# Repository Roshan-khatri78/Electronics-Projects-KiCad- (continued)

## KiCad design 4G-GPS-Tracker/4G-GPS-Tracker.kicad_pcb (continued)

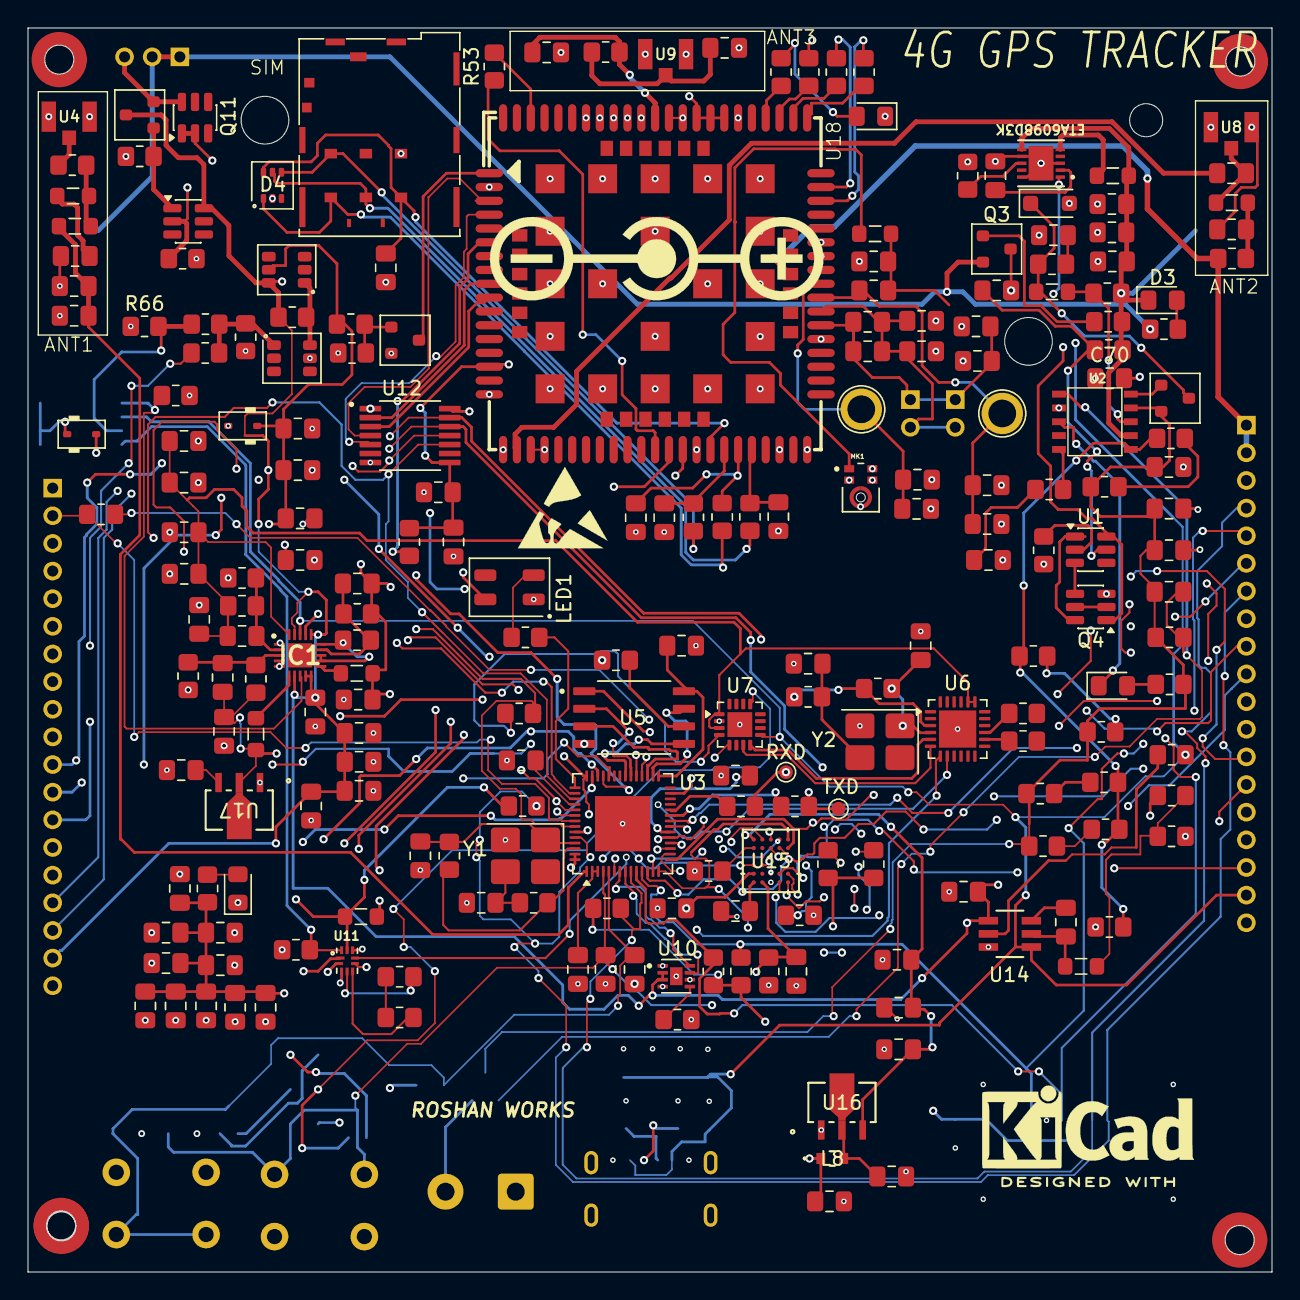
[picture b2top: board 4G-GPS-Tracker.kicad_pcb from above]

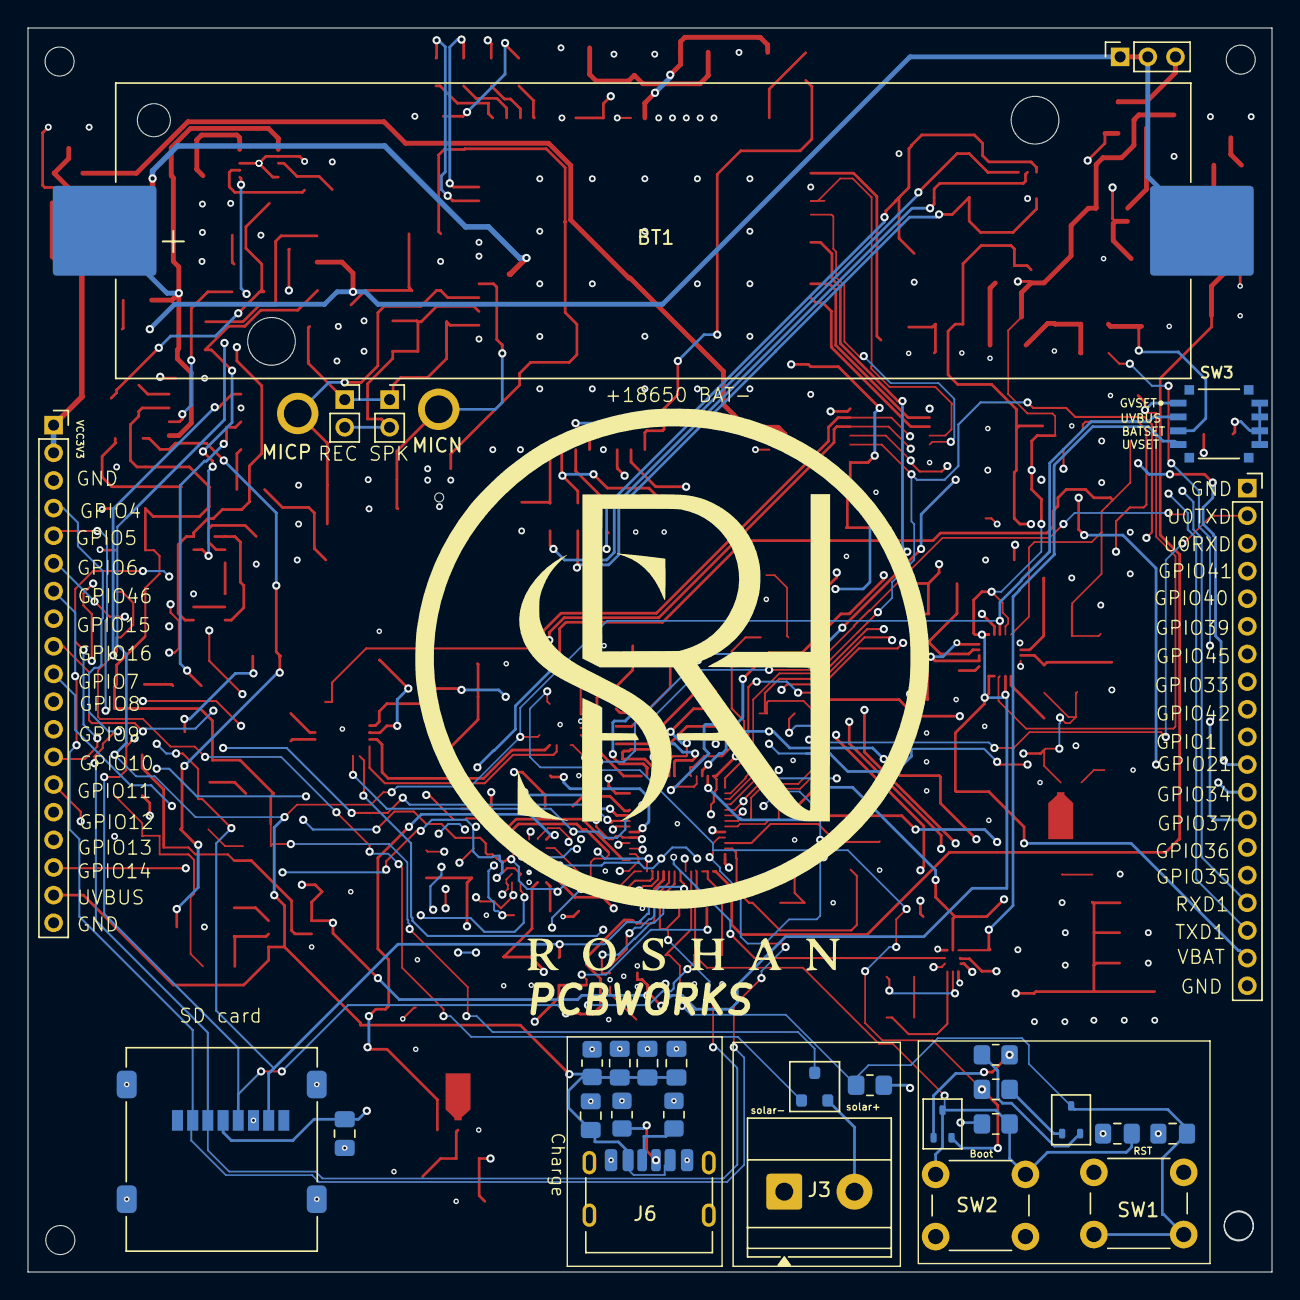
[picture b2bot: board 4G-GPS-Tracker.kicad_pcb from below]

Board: 4 copper layers, 90.0 x 90.0 mm, 248 parts (29 on the bottom side), 177 nets.

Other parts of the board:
ETA6098D3K: ETA6098D3K; DFN3x3-10_ETA-L
MICN: TestPoint; TestPoint_Plated_Hole_D2.0mm
MICP: TestPoint; TestPoint_Plated_Hole_D2.0mm
RXD: TestPoint; TestPoint_Pad_D1.0mm

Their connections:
/B+: ETA6098D3K.6 (BATS); also elsewhere on the board
/MIC N: MICN.1 (1_1); also elsewhere on the board
/MIC P: MICP.1 (1_1); also elsewhere on the board
/RXD1: RXD.1 (1_1); also elsewhere on the board
/UVBUS: ETA6098D3K.1 (IN); also elsewhere on the board
GND: ETA6098D3K.3 (PGND), ETA6098D3K.7 (AGND), ETA6098D3K.10 (AGND), ETA6098D3K.11 (AGND); also elsewhere on the board
unnamed 171: ETA6098D3K.8 (ISET); also elsewhere on the board
unnamed 172: ETA6098D3K.2 (PMID); also elsewhere on the board
unnamed 173: ETA6098D3K.5 (SW); also elsewhere on the board

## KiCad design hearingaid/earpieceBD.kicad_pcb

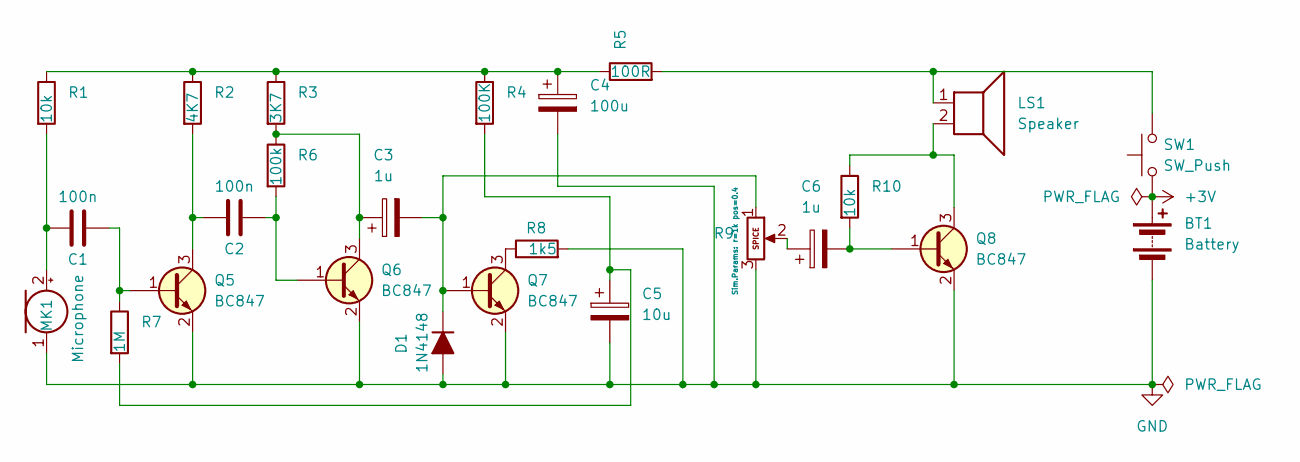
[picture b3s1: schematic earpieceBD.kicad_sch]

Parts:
BT1: Battery; BatteryHolder_Renata_SMTU2032-LF_1x2032
C1, C2: 100n; C_0805_2012Metric_Pad1.18x1.45mm_HandSolder
C3, C6: 1u; CP_EIA-3216-18_Kemet-A
C4: 100u; CP_Elec_5x5.4
C5: 10u; CP_EIA-3216-18_Kemet-A
D1: 1N4148; D_SOD-123
LS1: Speaker; SPKR_CVS-1708
MK1: Microphone; MIC_CMEJ-0415-42-P
Q5, Q6, Q7, Q8: BC847; SOT-23
R1, R10: 10k; R_0805_2012Metric_Pad1.20x1.40mm_HandSolder
R2: 4K7; R_0805_2012Metric_Pad1.20x1.40mm_HandSolder
R3: 3K7; R_0805_2012Metric_Pad1.20x1.40mm_HandSolder
R4: 100K; R_0805_2012Metric_Pad1.20x1.40mm_HandSolder
R5: 100R; R_0805_2012Metric_Pad1.20x1.40mm_HandSolder
R6: 100k; R_0805_2012Metric_Pad1.20x1.40mm_HandSolder
R7: 1M; R_0805_2012Metric_Pad1.20x1.40mm_HandSolder
R8: 1k5; R_0805_2012Metric_Pad1.20x1.40mm_HandSolder
R9: 22k; Potentiometer_Bourns_3314G_Vertical
SW1: SW_Push; SW_SPST_EVQP2_MiddlePushTravel_H2.5mm

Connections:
+3V: BT1.1 (+), SW1.1
GND: BT1.2 (-), C4.2, C5.2, D1.2 (A), MK1.1 (-), Q5.2 (E), Q6.2 (E), Q7.2 (E), Q8.2 (E), R8.2, R9.3
unnamed: C4.1, R1.1, R2.1, R3.1, R4.1, R5.1
unnamed: C5.1, R4.2, R7.2
unnamed: C6.1, R9.2
unnamed: C3.2, D1.1 (K), Q7.1 (B), R9.1
unnamed: LS1.1, R5.2, SW1.2
unnamed: C1.1, MK1.2 (+), R1.2
unnamed: C1.2, Q5.1 (B), R7.1
unnamed: C2.1, Q5.3 (C), R2.2
unnamed: C2.2, Q6.1 (B), R6.2
unnamed: C3.1, Q6.3 (C), R3.2, R6.1
unnamed: Q7.3 (C), R8.1
unnamed: C6.2, Q8.1 (B), R10.2
unnamed: LS1.2, Q8.3 (C), R10.1

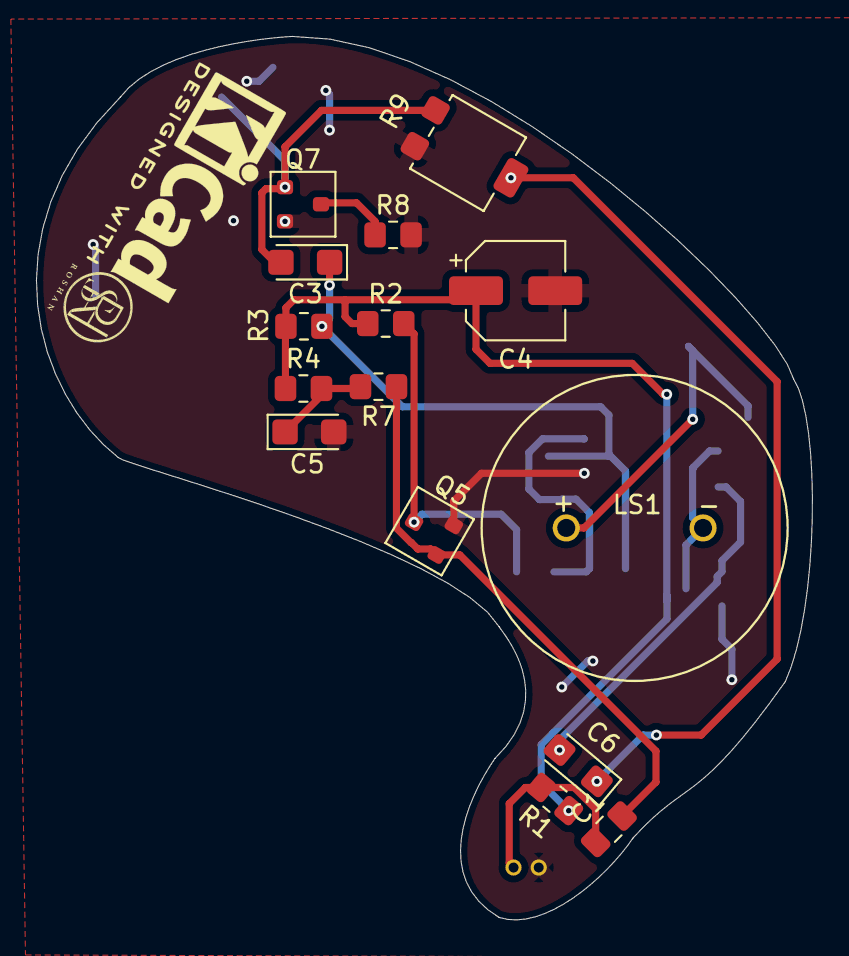
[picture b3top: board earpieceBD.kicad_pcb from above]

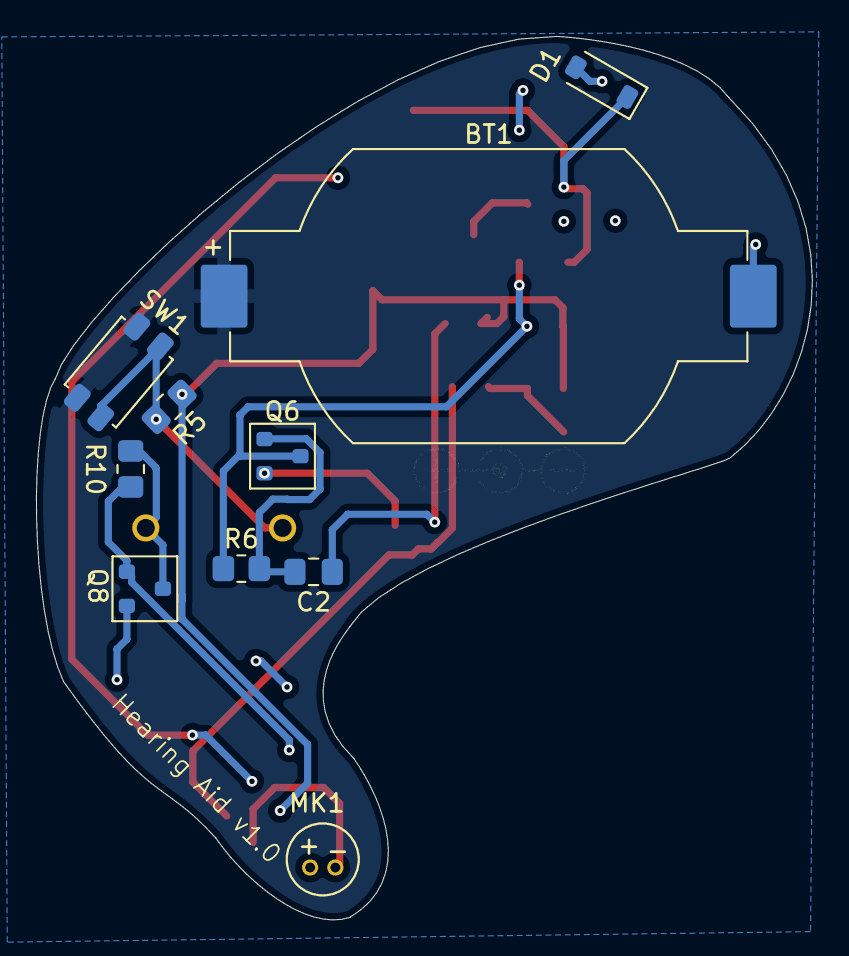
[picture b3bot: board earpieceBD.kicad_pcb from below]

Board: 4 copper layers, 43.1 x 49.1 mm, 25 parts (10 on the bottom side), 15 nets.

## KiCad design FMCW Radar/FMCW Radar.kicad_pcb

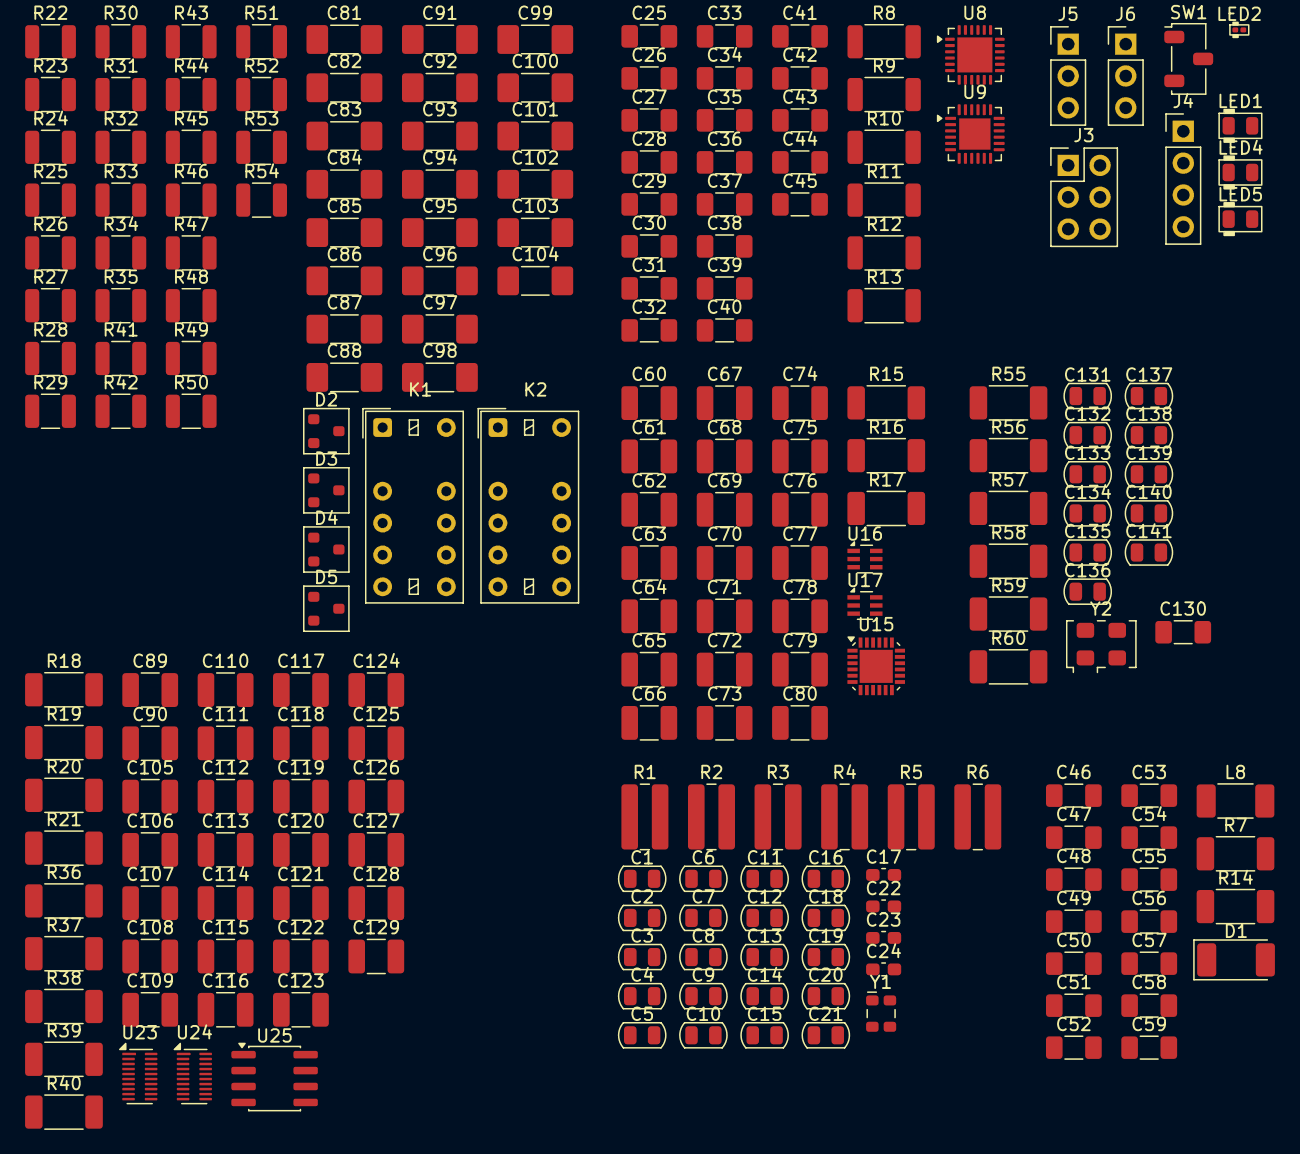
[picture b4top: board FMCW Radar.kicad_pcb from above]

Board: 2 copper layers, 228 parts (0 on the bottom side), 101 nets, no tracks yet.

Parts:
C1, C2, C7, C10, C140: 1u; C_0805_2012Metric
C3, C4, C5, C6, C9, C11, C16, C131, C133, C134, C136, C138, C139: 100n; C_0805_2012Metric
C8: 10on; C_0805_2012Metric
C12, C13, C14, C15, C18, C19, C20, C21: 4u7; C_0805_2012Metric
C17: C_0805; C_0603_1608Metric_Pad1.08x0.95mm_HandSolder
C22, C24: 10n; C_0603_1608Metric_Pad1.08x0.95mm_HandSolder
C23: 22n; C_0603_1608Metric_Pad1.08x0.95mm_HandSolder
C25, C26, C27, C28: 4U7; C_1206_3216Metric_Pad1.33x1.80mm_HandSolder
C29, C30, C31, C59: 10p; C_1206_3216Metric_Pad1.33x1.80mm_HandSolder
C32: 10n; C_1206_3216Metric_Pad1.33x1.80mm_HandSolder
C33: 4u7; C_1206_3216Metric_Pad1.33x1.80mm_HandSolder
C34: 180n; C_1206_3216Metric_Pad1.33x1.80mm_HandSolder
C35, C37, C38, C39, C40, C41, C42, C43, C44, C45: 15N; C_1206_3216Metric_Pad1.33x1.80mm_HandSolder
C36: 5n6; C_1206_3216Metric_Pad1.33x1.80mm_HandSolder
C46, C56: 100P; C_1206_3216Metric_Pad1.33x1.80mm_HandSolder
C47, C48, C53, C54, C130: 2u2; C_1206_3216Metric_Pad1.33x1.80mm_HandSolder
C49, C50, C51, C52, C55: 100n; C_1206_3216Metric_Pad1.33x1.80mm_HandSolder
C57: 200f; C_1206_3216Metric_Pad1.33x1.80mm_HandSolder
C58: 5p6; C_1206_3216Metric_Pad1.33x1.80mm_HandSolder
C60, C61, C62, C63: 3p; C_1210_3225Metric_Pad1.33x2.70mm_HandSolder
C64: 10P; C_1210_3225Metric_Pad1.33x2.70mm_HandSolder
C65: 10p; C_1210_3225Metric_Pad1.33x2.70mm_HandSolder
C66, C67, C70, C71, C75, C76, C80, C89, C107, C110, C112, C114, C115, C119, C120, C123, C124: 100n; C_1210_3225Metric_Pad1.33x2.70mm_HandSolder
C68, C69, C79: 100p; C_1210_3225Metric_Pad1.33x2.70mm_HandSolder
C72, C117, C121, C126, C128: 4u7; C_1210_3225Metric_Pad1.33x2.70mm_HandSolder
C73, C74, C118, C122, C127, C129: 2u2; C_1210_3225Metric_Pad1.33x2.70mm_HandSolder
C77, C78: 82n; C_1210_3225Metric_Pad1.33x2.70mm_HandSolder
C81, C82, C92, C96: 1u; C_1808_4520Metric_Pad1.72x2.30mm_HandSolder
C83, C84, C86, C88, C91, C94, C95, C100: 33n; C_1808_4520Metric_Pad1.72x2.30mm_HandSolder
C85, C87, C93, C99, C103, C104: 1n1; C_1808_4520Metric_Pad1.72x2.30mm_HandSolder
C90: 10N; C_1210_3225Metric_Pad1.33x2.70mm_HandSolder
C97, C98, C101, C102: 100n; C_1808_4520Metric_Pad1.72x2.30mm_HandSolder
C105: 1U; C_1210_3225Metric_Pad1.33x2.70mm_HandSolder
C106, C116, C125: 1u; C_1210_3225Metric_Pad1.33x2.70mm_HandSolder
C108, C109, C111, C113: 1n; C_1210_3225Metric_Pad1.33x2.70mm_HandSolder
C132, C135, C137, C141: 2u2; C_0805_2012Metric
D1: LED; LED_2010_5025Metric_Pad1.52x2.65mm_HandSolder
D2, D3, D4, D5: BAR46; SOT-23
J3: Conn_02x03_Odd_Even; PinHeader_2x03_P2.54mm_Vertical
J4: Conn_01x04; PinHeader_1x04_P2.54mm_Vertical
J5, J6: Conn_01x03; PinHeader_1x03_P2.54mm_Vertical
K1, K2: EC2-4.5TNU; Relay_DPDT_Kemet_EC2_NU_DoubleCoil
L8: 18n; L_2010_5025Metric_Pad1.52x2.65mm_HandSolder
LED1: LED_0805_Amber; LED_0805_2012Metric
LED2: LED_0201_Red; LED_0201_0603Metric
LED4, LED5: LED_0805_Green; LED_0805_2012Metric
R1, R2, R3, R4: 40K; R_1020_2550Metric_Pad1.33x5.20mm_HandSolder
R5, R6: 470k; R_1020_2550Metric_Pad1.33x5.20mm_HandSolder
R7: 3K9; R_2010_5025Metric_Pad1.40x2.65mm_HandSolder
R8: 49r9; R_2010_5025Metric
R9, R10: 180R; R_2010_5025Metric
R11: 45R3; R_2010_5025Metric
R12: 27r; R_2010_5025Metric
R13: 5K1; R_2010_5025Metric
R14: 680R; R_2010_5025Metric_Pad1.40x2.65mm_HandSolder
R15, R16: 49R9; R_2010_5025Metric_Pad1.40x2.65mm_HandSolder
R17: 665R; R_2010_5025Metric_Pad1.40x2.65mm_HandSolder
R18, R38: 40K; R_2010_5025Metric_Pad1.40x2.65mm_HandSolder
R19: 27r; R_2010_5025Metric_Pad1.40x2.65mm_HandSolder
R20: 1k5; R_2010_5025Metric_Pad1.40x2.65mm_HandSolder
R21: 19r9; R_2010_5025Metric_Pad1.40x2.65mm_HandSolder
R22, R23, R32, R33, R43, R44, R49, R50: 160R; R_1210_3225Metric
R24, R25, R30, R31, R41, R42, R47, R48: 240R; R_1210_3225Metric
R26, R29: 360R; R_1210_3225Metric
R27, R28, R34, R35, R45, R46, R51, R52: 481R; R_1210_3225Metric
R36, R37: 49r9; R_2010_5025Metric_Pad1.40x2.65mm_HandSolder
R39: 8K2; R_2010_5025Metric_Pad1.40x2.65mm_HandSolder
R40: 4K22; R_2010_5025Metric_Pad1.40x2.65mm_HandSolder
R53, R54: 4K22; R_1210_3225Metric
R55, R59: 10k; R_2010_5025Metric_Pad1.40x2.65mm_HandSolder
R56: 5k1; R_2010_5025Metric_Pad1.40x2.65mm_HandSolder
R57: 100k; R_2010_5025Metric_Pad1.40x2.65mm_HandSolder
R58: 0R; R_2010_5025Metric_Pad1.40x2.65mm_HandSolder
R60: 39R; R_2010_5025Metric_Pad1.40x2.65mm_HandSolder
SW1: SW_SPDT; Nidec_Copal_CAS-120A
U8: HMC431; QFN-24-1EP_4x4mm_P0.5mm_EP2.8x2.8mm
U9: ADF4158; LFCSP-24-1EP_4x4mm_P0.5mm_EP2.5x2.5mm
U15: ADL5801; LFCSP-VQ-24-1EP_4x4mm_P0.5mm_EP2.642x2.642mm
U16, U17: 5400BL15B050; Balun_Johanson_5400BL15B050E
U23, U24: TXB0108DQSR; USON-20_2x4mm_P0.4mm
U25: INA849D; SOIC-8_3.9x4.9mm_P1.27mm
Y1: TG2520SMN-xx.xxxxxxMhz-xxxxNM; Oscillator_SMD_SeikoEpson_TG2520SMN-xxx-xxxxxx-4Pin_2.5x2.0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
Y2: TXC-7C; Oscillator_SMD_TXC_7C-4Pin_5.0x3.2mm

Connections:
+3V3A: C38.2, C39.2, C40.2, C47.1, C50.1, U9.6 (AVDD), U9.7 (AVDD), U9.8 (AVDD)
+3V3D: C5.1, C6.1, C7.1, C8.1, C9.1, C10.1, C11.1, C12.1, C13.1, C17.1, C41.1, C42.1, C43.1, C121.1, C138.2, C139.2, C140.2, C141.2, J3.4, J5.1, J6.1, LED1.2 (A), LED2.2 (A), LED4.2 (A), LED5.2 (A), SW1.1 (A)
+3VA: C32.2, C33.2, U8.20 (VCC)
+5V-ADC: C107.1, C108.1, C109.1, C110.1, C111.1, C112.1, C127.1, U25.8 (Vs+)
+5VA: C25.1, C26.1, C53.1, C126.1, R17.2
+5VD: C113.1, C114.1, C117.1, C136.2, C137.2, D2.3 (K), D3.3 (K), D4.3 (K), D5.3 (K), K1.7, K1.12, K2.7, K2.12
-5V-ADC: C89.1, C115.1, C116.1, C125.1, C129.1, U25.5 (Vs-)
/U_MCU/CLK-VDD: C18.1, C19.1, C20.1, C21.1
/U_MCU/MCU-VDDA: C1.1, C2.1, C3.1, C4.1
/U_RxADC/ADC-CLK: U23.3 (A3), U23.11 (B8)
/U_RxADC/ADC-GAIN: U23.2 (A2), U23.12 (B7)
/U_RxADC/ADC-IF N: K2.4, R36.1, U25.4 (+)
/U_RxADC/ADC-IF P: K2.9, R21.2, U25.1 (-)
/U_RxADC/ADC-OF: R39.1, R40.1, R40.2
/U_RxADC/LVL1-OE: R38.1, U24.6 (OE)
/U_RxADC/LVL2-OE: R18.1, U23.6 (OE)
/U_RxADC/LVL-VCCA: C122.1, C123.1, C124.1, U23.5 (VCCA), U24.5 (VCCA)
/U_RxADC/LVL-VCCB: C118.1, C119.1, C120.1, U23.16 (VCCB), U24.16 (VCCB)
/U_RxFrontEnd/LNA2-EN: C59.2, R14.2
/U_RxIFStage/FILT-LR-OUT N: C101.2, K2.10
/U_RxIFStage/FILT-LR-OUT P: C102.2, K2.3
/U_RxIFStage/FILT-RST: D2.1 (A), D3.1 (A), K1.6, K2.6
/U_RxIFStage/FILT-SET: D4.1 (A), D5.1 (A), K1.1, K2.1
/U_RxIFStage/FILT-SR-IN N: K1.8, K1.10, R24.1, R26.2, R29.1, R31.1
/U_RxIFStage/FILT-SR-IN P: K1.3, K1.5, R25.1, R26.1, R29.2, R30.1
/U_RxIFStage/FILT-SR-OUT N: C97.2, K2.8
/U_RxIFStage/FILT-SR-OUT P: C98.2, K2.5
/U_RxMixer/BALLUN-LO N: C61.1, U17.3
/U_RxMixer/BALLUN-LO P: C60.1, U17.4
/U_RxMixer/BALLUN-RF N: C62.1, U16.4
/U_RxMixer/BALLUN-RF P: C63.1, U16.3
/U_RxMixer/MIX-LO N: C61.2, U15.3 (LOIP)
/U_RxMixer/MIX-LO P: C60.2, U15.4 (LOIN)
/U_RxMixer/MIX-RF N: C62.2, U15.15 (RFIN)
/U_RxMixer/MIX-RF P: C63.2, U15.16 (RFIP)
/U_StatusAndInputOutput/BOOT0: J5.2, R2.1
/U_StatusAndInputOutput/BOOT1: J6.2, R4.2
/U_StatusAndInputOutput/MISC1: J4.2, J4.4
/U_StatusAndInputOutput/SWD-NRST: C16.1, J3.2
/U_StatusAndInputOutput/TX/STDBY: R1.2, SW1.2 (B)
GND: C1.2, C2.2, C3.2, C4.2, C5.2, C6.2, C7.2, C8.2, C9.2, C10.2, C11.2, C12.2, C13.2, C14.2, C15.2, C16.2, C17.2, C18.2, C19.2, C20.2, C21.2, C22.2, C24.1, C25.2, C26.2, C27.2, C28.2, C30.2, C31.1, C32.1, C33.1, C35.1, C36.1, C37.1, C38.1, C39.1, C40.1, C41.2, C42.2, C43.2, C44.2, C45.2, C46.2, C47.2, C48.2, C49.2, C50.2, C52.1, C53.2, C54.2, C55.2, C56.2, C57.2, C59.1, C66.2, C67.2, C68.2, C69.2, C70.2, C71.2, C72.2, C73.2, C74.2, C75.2, C76.2, C79.1, C80.1, C81.2, C82.2, C89.2, C90.2, C92.2, C96.2, C103.1, C104.1, C105.2, C106.2, C107.2, C108.2, C109.2, C110.2, C111.2, C112.2, C113.2, C114.2, C115.2, C116.2, C117.2, C118.2, C119.2, C120.2, C121.2, C122.2, C123.2, C124.2, C125.2, C126.2, C127.2, C128.2, C129.2, C130.2, C131.1, C132.1, C133.1, C134.1, C135.1, C136.1, C137.1, C138.1, C139.1, C140.1, C141.1, D1.1 (K), J3.3, J4.1, J4.3, J5.3, J6.3, R3.2, R8.2, R10.1, R13.1, R18.2, R37.1, R38.2, R56.1, R58.1, R59.2, SW1.3 (C), U8.15 (GND), U8.25 (GND), U9.1 (CPGND), U9.2 (AGND), U9.3 (AGND), U9.10 (DGND), U9.11 (SDGND), U9.18 (SDVDD), U9.19 (DVDD), U9.25 (AGND), U15.1 (GND), U15.2 (GND), U15.5 (GND), U15.6 (GND), U15.8 (GND), U15.12 (GND), U15.14 (GND), U15.17 (GND), U15.19 (GND), U15.23 (GND), U15.25 (GND), U16.2 (GND), U16.5 (GND), U17.2 (GND), U17.5 (GND), U23.15 (GND), U24.15 (GND), U25.6 (Ref), Y1.2 (GND), Y2.2 (GND)
unnamed: C22.1, R5.1, R6.2
unnamed: C34.1, R10.2, R12.1
unnamed: C34.2, C35.2, R9.1
unnamed: C44.1, C45.1
unnamed: C46.1, C48.1, C49.1
unnamed: C54.1, C55.1, C56.1, L8.1, R7.2
unnamed: C64.2, U17.1
unnamed: C65.2, U16.1
unnamed: C72.1, C73.1, C74.1, C75.1, C76.1, R15.1, R16.1
unnamed: C83.1, R23.1, R24.2, R28.1
unnamed: C83.2, R22.1, R25.2, R27.1
unnamed: C86.1, R30.2, R32.1, R34.1
unnamed: C86.2, R31.2, R33.1, R35.1
unnamed: C91.1, R41.2, R43.1, R45.1
unnamed: C91.2, R42.2, R44.1, R46.1
unnamed: C95.1, R47.2, R49.1, R51.1
unnamed: C95.2, R48.2, R50.1, R52.1
unnamed: C130.1, R55.2, R57.2
unnamed: D1.2 (A), R14.1
unnamed: C103.2, R53.2
unnamed: C104.2, R54.2
unnamed: R19.1, U25.7
unnamed: R20.1, U25.3 (Rg)
unnamed: R20.2, U25.2 (Rg)
unnamed: R21.1, R36.2, R37.2
unnamed: C23.2, R5.2
unnamed: C27.1, C28.1
unnamed: C36.2, R9.2, R11.2, U8.22 (VTUNE)
unnamed: C37.2, U9.4 (RFINB)
unnamed: R13.2, U9.23 (RSET)
unnamed: R12.2, U9.20 (SW1)
unnamed: R11.1, U9.21 (SW2)
unnamed: C57.1, C58.2
unnamed: C51.1, C52.2, L8.2
unnamed: C78.1, R15.2, U15.21 (IFON)
unnamed: C77.1, R16.2, U15.20 (IFOP)
unnamed: C66.1, C67.1, C68.1, C69.1, C70.1, C71.1, U15.7 (VPLO), U15.13 (VPDT), U15.18 (VPRF), U15.24 (VPLO)
unnamed: C79.2, C80.2, R17.1, U15.10 (VSET)
unnamed: C85.1, R23.2
unnamed: C84.1, R22.2
unnamed: C84.2, R28.2, R41.1
unnamed: C85.2, R27.2, R42.1
unnamed: C87.1, R32.2
unnamed: C88.1, R33.2
unnamed: C88.2, R34.2, R47.1
unnamed: C87.2, R35.2, R48.1
unnamed: C93.1, R43.2
unnamed: C94.1, R44.2
unnamed: C94.2, C97.1, R45.2
unnamed: C93.2, C98.1, R46.2
unnamed: C99.1, R49.2
unnamed: C100.1, R50.2
unnamed: C100.2, C102.1, R51.2
unnamed: C99.2, C101.1, R52.2
unnamed: C90.1, R19.2
unnamed: C132.2, C133.2
unnamed: C134.2, C135.2
unnamed: C23.1, Y1.3 (OUT)
unnamed: C24.2, Y1.4 (Vcc)
unnamed: C131.2, Y2.4 (Vdd)

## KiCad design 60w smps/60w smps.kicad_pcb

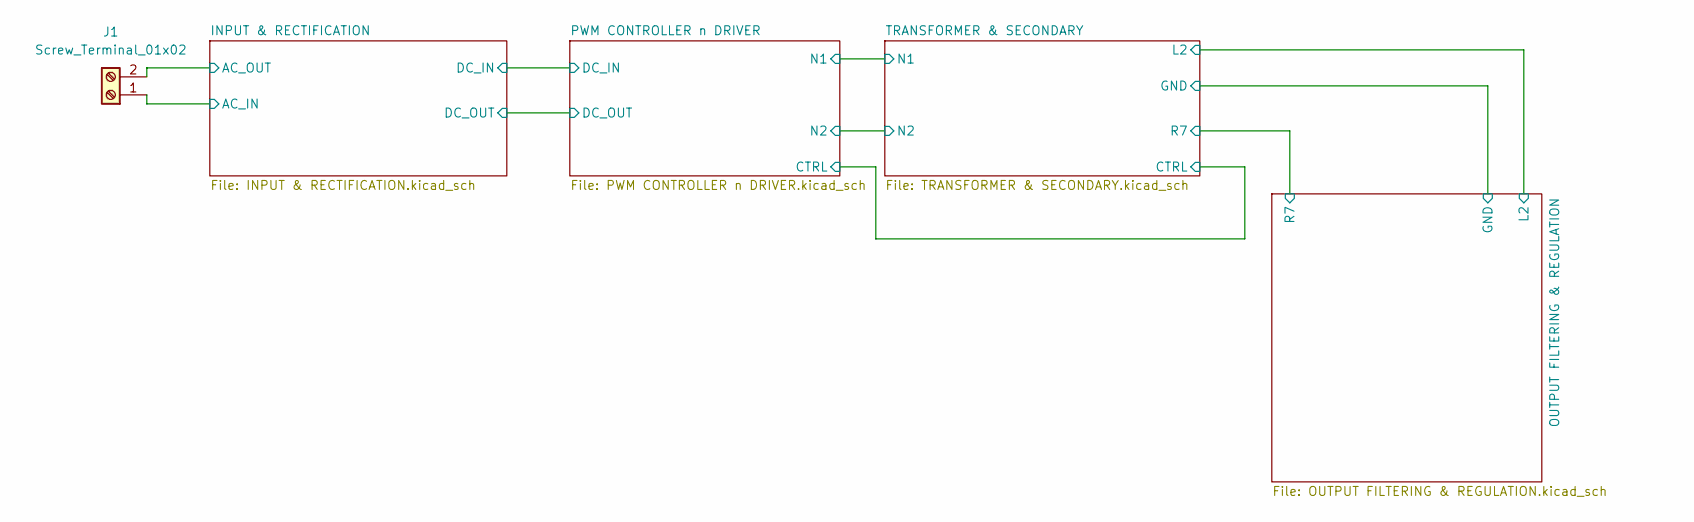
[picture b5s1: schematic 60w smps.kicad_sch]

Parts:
J1: Screw_Terminal_01x02; TerminalBlock_MaiXu_MX126-5.0-02P_1x02_P5.00mm

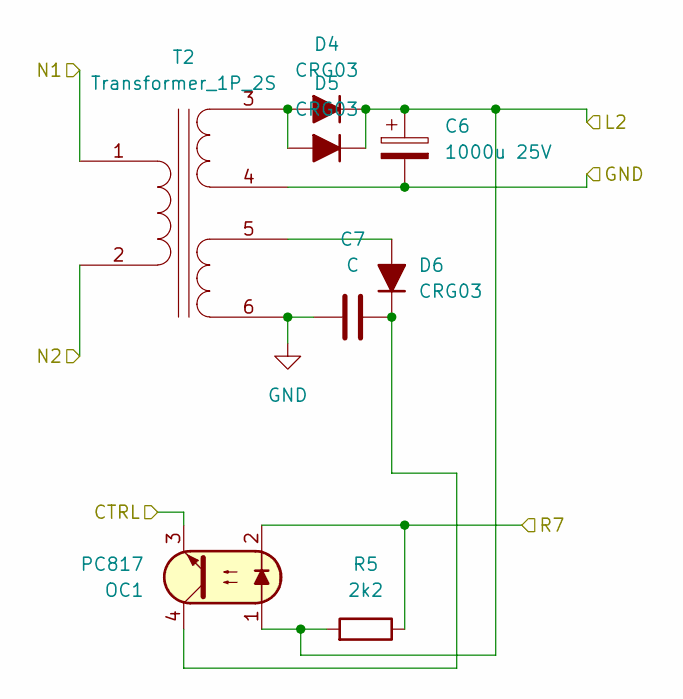
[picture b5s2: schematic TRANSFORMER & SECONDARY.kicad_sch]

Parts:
C6: 1000u 25V; CP_Elec_8x10
C7: C; C_0805_2012Metric_Pad1.18x1.45mm_HandSolder
D4, D5, D6: CRG03; D_SOD-123F
OC1: PC817; DIP-4_W7.62mm_LongPads
R5: 2k2; R_0805_2012Metric_Pad1.20x1.40mm_HandSolder
T2: Transformer_1P_2S; WE-IBTI_EP7_L9.78W9.5H10.54

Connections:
/INPUT & RECTIFICATION/DC_IN: T2.1 (AA); also elsewhere on the board
/OUTPUT FILTERING & REGULATION/L2: C6.1, D4.1 (K), D5.1 (K), OC1.1, R5.1; also elsewhere on the board
/OUTPUT FILTERING & REGULATION/R7: OC1.2, R5.2; also elsewhere on the board
/PWM CONTROLLER n DRIVER/CTRL: OC1.3; also elsewhere on the board
/PWM CONTROLLER n DRIVER/N2: T2.2 (AB); also elsewhere on the board
GND: C6.2, C7.1, T2.4 (SB), T2.6 (SD); also elsewhere on the board
unnamed: D4.2 (A), D5.2 (A), T2.3 (SA)
unnamed: D6.2 (A), T2.5 (SC)
unnamed: C7.2, D6.1 (K), OC1.4

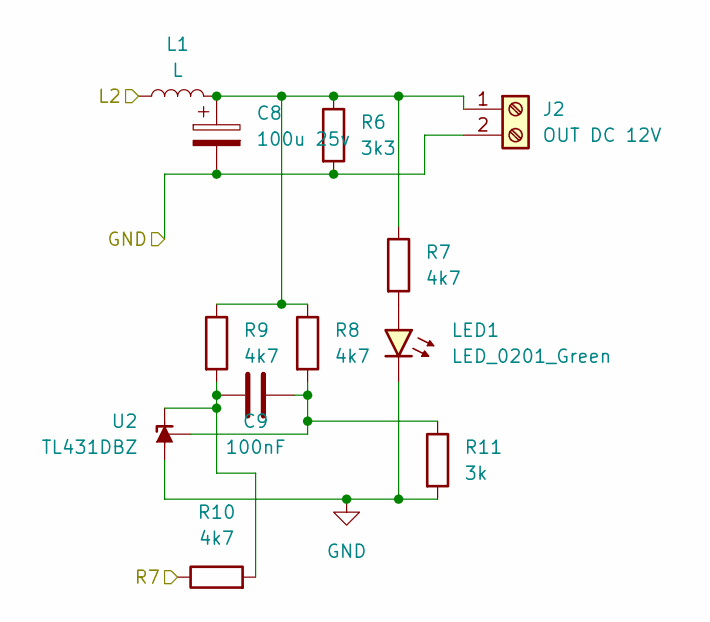
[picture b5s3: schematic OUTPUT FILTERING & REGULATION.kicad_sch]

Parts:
C8: 100u 25v; CP_Radial_D16.0mm_P7.50mm
C9: 100nF; C_1808_4520Metric_Pad1.72x2.30mm_HandSolder
J2: OUT DC 12V; TerminalBlock_MaiXu_MX126-5.0-02P_1x02_P5.00mm
L1: L; L_1008_2520Metric_Pad1.43x2.20mm_HandSolder
LED1: LED_0201_Green; LED_0201_0603Metric
R6: 3k3; R_0603_1608Metric_Pad0.98x0.95mm_HandSolder
R7, R8, R9, R10: 4k7; R_0603_1608Metric_Pad0.98x0.95mm_HandSolder
R11: 3k; R_0603_1608Metric_Pad0.98x0.95mm_HandSolder
U2: TL431DBZ; SOT-23

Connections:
/OUTPUT FILTERING & REGULATION/L2: L1.1; also elsewhere on the board
/OUTPUT FILTERING & REGULATION/R7: R10.1; also elsewhere on the board
GND: C8.2, J2.2, LED1.1 (K), R6.2, R11.2, U2.3 (A); also elsewhere on the board
unnamed 17: C8.1, J2.1, L1.2, R6.1, R7.1, R8.1, R9.1; also elsewhere on the board
unnamed: LED1.2 (A), R7.2
unnamed: C9.1, R9.2, R10.2, U2.1 (K)
unnamed: C9.2, R8.2, R11.1, U2.2 (REF)

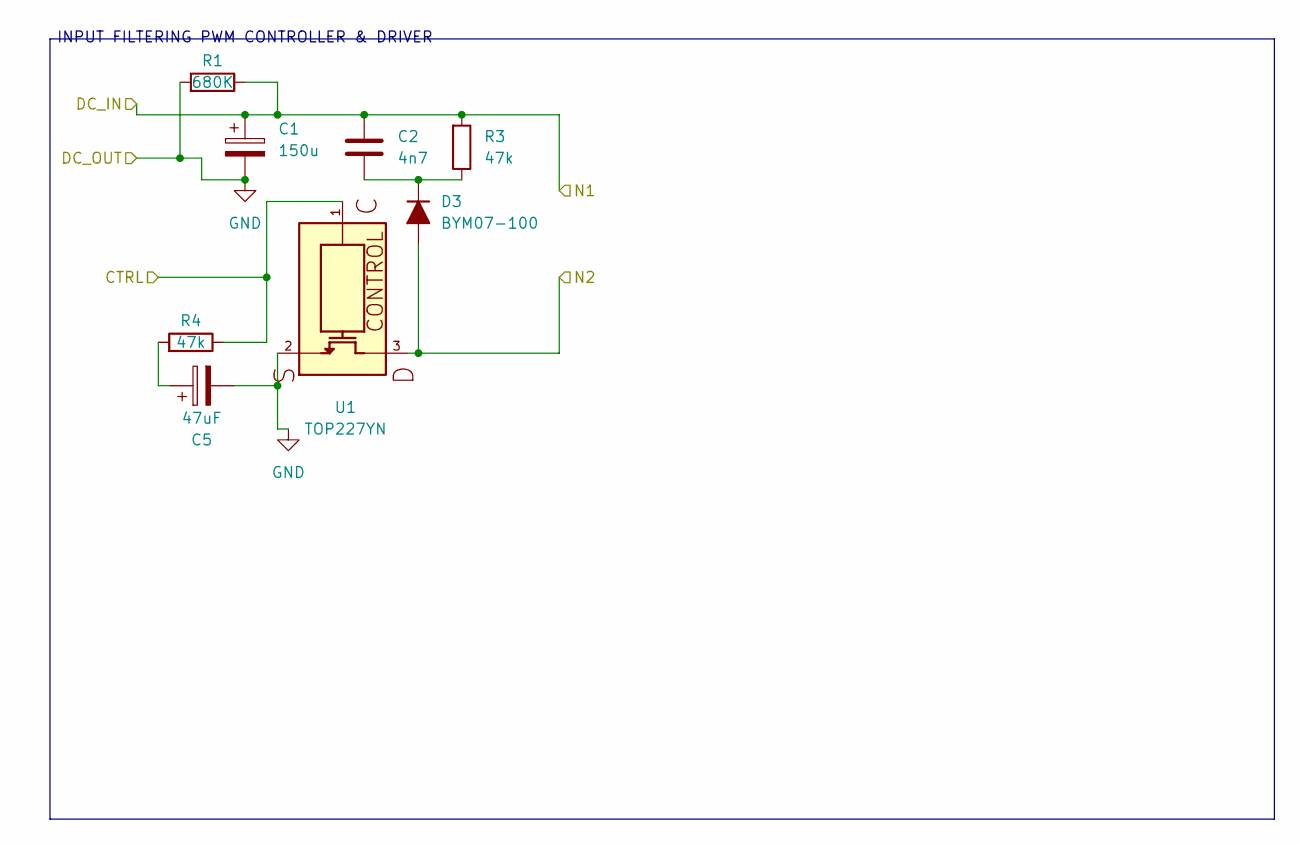
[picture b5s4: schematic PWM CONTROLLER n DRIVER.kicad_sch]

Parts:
C1: 150u; CP_Radial_D10.0mm_P3.50mm
C2: 4n7; C_Axial_L12.0mm_D10.5mm_P15.00mm_Horizontal
C5: 47uF; CP_Radial_D10.0mm_P3.50mm
D3: BYM07-100; D_MiniMELF
R1: 680K; R_0805_2012Metric_Pad1.20x1.40mm_HandSolder
R3, R4: 47k; R_Axial_DIN0414_L11.9mm_D4.5mm_P15.24mm_Horizontal
U1: TOP227YN; TO254P1035X444X2115-3N; PARTREV G

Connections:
/INPUT & RECTIFICATION/DC_IN: C1.1, C2.1, R1.2, R3.1; also elsewhere on the board
/PWM CONTROLLER n DRIVER/CTRL: R4.2, U1.1; also elsewhere on the board
/PWM CONTROLLER n DRIVER/N2: D3.2 (A), U1.3; also elsewhere on the board
GND: C1.2, C5.2, R1.1, U1.2; also elsewhere on the board
unnamed: C5.1, R4.1
unnamed: C2.2, D3.1 (K), R3.2

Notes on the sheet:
INPUT FILTERING PWM CONTROLLER & DRIVER

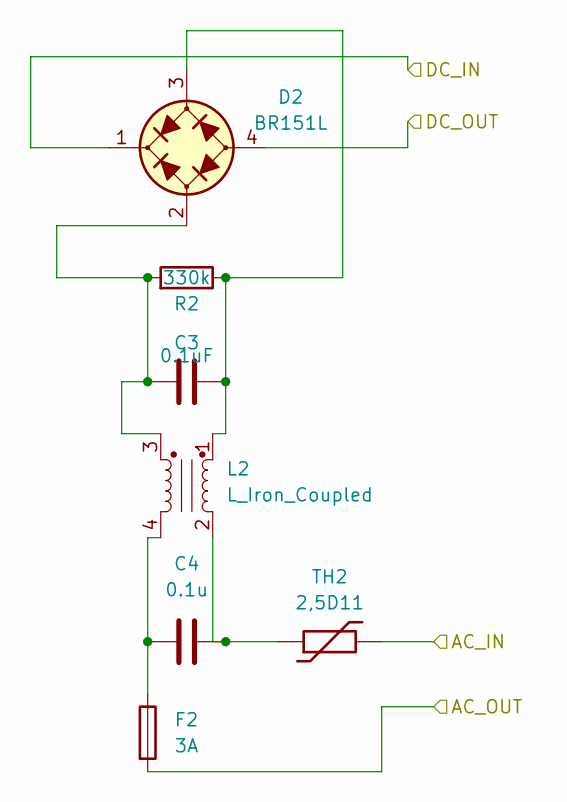
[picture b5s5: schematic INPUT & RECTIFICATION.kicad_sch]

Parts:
C3: 0.1uF; C_2220_5750Metric
C4: 0.1u; C_Axial_L12.0mm_D6.5mm_P20.00mm_Horizontal
D2: BR151L; Diode_Bridge_28.6x28.6x7.3mm_P5.08mm_Vertical
F2: 3A; Fuse_2010_5025Metric_Pad1.52x2.65mm_HandSolder
L2: L_Iron_Coupled; WE-MCRI_1040
R2: 330k; R_0805_2012Metric_Pad1.20x1.40mm_HandSolder
TH2: 2,5D11; R_0815_2038Metric_Pad1.53x4.00mm_HandSolder

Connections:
/INPUT & RECTIFICATION/AC_IN: TH2.2; also elsewhere on the board
/INPUT & RECTIFICATION/AC_OUT: F2.2; also elsewhere on the board
/INPUT & RECTIFICATION/DC_IN: D2.1 (+); also elsewhere on the board
GND: D2.4 (-); also elsewhere on the board
unnamed: C4.1, F2.1, L2.4
unnamed: C4.2, L2.2, TH2.1
unnamed: C3.1, D2.2 (1), L2.3, R2.1
unnamed: C3.2, D2.3 (2), L2.1, R2.2

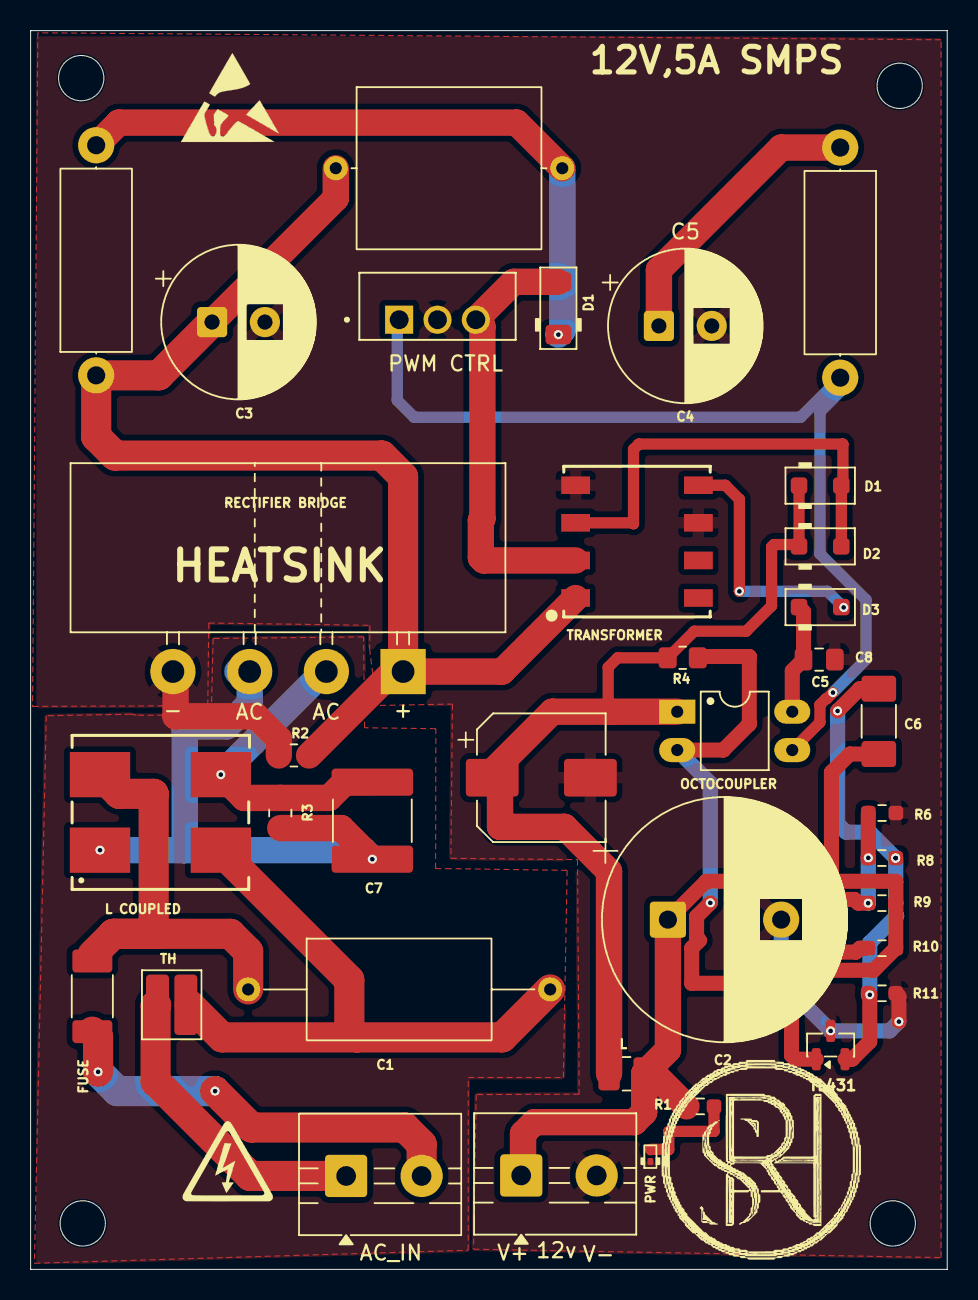
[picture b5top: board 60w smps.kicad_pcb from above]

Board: 2 copper layers, 60.7 x 82.0 mm, 37 parts (0 on the bottom side), 21 nets.

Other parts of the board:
AC_IN: Screw_Terminal_01x02; TerminalBlock_MaiXu_MX126-5.0-02P_1x02_P5.00mm
V+: OUT DC 12V; TerminalBlock_MaiXu_MX126-5.0-02P_1x02_P5.00mm
s: LOGO; electric_Shock

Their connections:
/INPUT & RECTIFICATION/AC_IN: AC_IN.1; also elsewhere on the board
/INPUT & RECTIFICATION/AC_OUT: AC_IN.2; also elsewhere on the board
GND: V+.2; also elsewhere on the board
unnamed 17: V+.1; also elsewhere on the board
